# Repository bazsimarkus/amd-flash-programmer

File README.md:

# amd-flash-programmer
A simple Arduino-based flash memory programmer for AM29F010 and AM29F040B series flash chips.

---

## Table of Contents

- [Overview](#overview)
- [Features](#features)
- [Hardware](#hardware)
  - [Schematic](#schematic)
  - [How It Works](#how-it-works)
  - [Bill of Materials](#bill-of-materials)
  - [Pin Mapping](#pin-mapping)
  - [Supported Chips](#supported-chips)
  - [PCB](#pcb)
- [Firmware](#firmware)
  - [Architecture](#architecture)
  - [Serial Protocol](#serial-protocol)
  - [Uploading the Firmware](#uploading-the-firmware)
- [Client Software](#client-software)
  - [Installation](#installation)
  - [Usage](#usage)
- [How to Use](#how-to-use)
  - [Connect](#connect)
  - [Read Chip ID](#read-chip-id)
  - [Read Memory](#read-memory)
  - [Erase Chip](#erase-chip)
  - [Write File](#write-file)
  - [Verify](#verify)
- [Performance](#performance)
- [Known Limitations & Future Ideas](#known-limitations--future-ideas)
- [Personal Notes](#personal-notes)
- [Inspirations & Credits](#inspirations--credits)

---

## Overview

I always needed a way to program AM29F040B flash chips without spending money on an expensive universal programmer. My [ATmega32-based MOD tracker player](https://github.com/bazsimarkus/avr-mod-player) uses this chip to store `.mod` tracker files, and to be able to write new music onto the player I decided to design a dedicated programmer board. These chips were also used in Game Boy Color cartridges, among other things, so there is a retro community out there that might find this useful too.

My main inspiration was [TommyPROM](https://github.com/TomNisbet/TommyPROM), but TommyPROM is a general-purpose EEPROM programmer and doesn't directly support the AMD 29F-series flash command sequences. The AM29F010 and AM29F040B use software-controlled erase and programming cycles with specific unlock addresses - you can't just write to them like a parallel EEPROM. So I designed my own board, wrote the Arduino firmware from scratch, and also created a Python GUI client to make the whole process beginner-friendly.

The result is a simple, easy-to-build board that does exactly what I need: read, write, erase, and verify AM29F-series flash chips over USB.

---

## Features

- **Read** - full chip or custom hex address range, displayed in a live hex viewer
- **Write** - binary files to flash with byte-by-byte handshake protocol
- **Erase** - full chip erase with proper DQ7 data polling
- **Verify** - automatic post-write verification or manual verify against any file
- **Chip ID** - reads manufacturer and device ID via autoselect mode
- **Hex Viewer** - colour-coded hex dump with ASCII column in the GUI
- **Event Log** - timestamped log of all operations, exportable to file
- **COM port auto-detection** - scans and lists available serial ports
- Supports **AM29F010** (128 KB) and **AM29F040B** (512 KB)
- Beginner-friendly - easy to solder, easy to flash, easy to use
- All through-hole components - no SMD soldering required
- Powered directly from USB via the Arduino Nano

---

## Hardware

### Schematic

The full KiCad project including schematic, PCB layout, and netlist is available in the `schematic/` folder.

---

### How It Works

The circuit is straightforward. There are only a few building blocks, and each has a clear job.

**Arduino Nano (A1)** - This is the brain of the board. It handles USB serial communication with the PC at 115200 baud, generates the timing for the shift registers, drives the flash chip's control signals (CE#, OE#, WE#), and reads/writes the 8-bit data bus. It is powered directly from the USB cable, and provides 5V to the rest of the circuit from its onboard regulator.

**74HC595 Shift Registers (U2, U3)** - The AM29F040B has 19 address lines (A0-A18), which is far more than what the Arduino Nano has available as spare GPIO. The solution is to use two 74HC595 shift registers daisy-chained together. These are 8-bit serial-in, parallel-out shift registers. The Arduino sends 16 bits of address data serially using just three control lines (serial data on A5, shift clock on A3, and latch clock on A4), and the two shift registers present all 16 bits simultaneously on their parallel outputs. U2 provides address lines A0-A7 (low byte), and its serial overflow output (QH') feeds into U3 which provides A8-A15 (high byte). The remaining three address lines (A16, A17, A18) are driven directly from the Nano's analog pins A0, A1, and A2 - there is no need to shift those since there are only three of them and the Nano has enough free pins.

**Flash Chip Socket (U1)** - A 32-pin ZIF (Zero Insertion Force) Textool socket. ZIF sockets have a lever that opens and closes the contacts, so you can insert and remove DIP chips without bending any pins. This is important because if you are regularly swapping flash chips in and out, a standard friction-fit DIP socket will eventually damage the pins or wear out. The ZIF socket is the most expensive component on the board, but it is worth it.

**Data Bus (D2-D9)** - The flash chip's 8-bit data bus (DQ0-DQ7) connects directly to Arduino Nano pins D2 through D9. These pins are mapped to PORTD bits 2-7 and PORTB bits 0-1 in the firmware. During a read, the Arduino sets these as inputs and reads the parallel data from the flash. During a write, it sets them as outputs and drives the data to be programmed.

**Control Signals (D10, D11, D12)** - Three active-low control signals go from the Arduino to the flash chip:
- **CE#** (Chip Enable) on D10 - must be low for the chip to respond to any bus cycle
- **OE#** (Output Enable) on D11 - drives the chip's data outputs onto the bus during a read
- **WE#** (Write Enable) on D12 - latches data into the chip during a write or command cycle

All three have 10kΩ pull-up resistors (R1, R2, R3) to +5V. This is a safety measure: during Arduino power-up, reset, or bootloader execution, the GPIO pins are momentarily tri-stated (floating). Without the pull-ups, the flash chip might interpret random noise on CE#, OE#, and WE# as valid bus cycles and get confused or, in a worst case, accidentally erase data. The pull-ups ensure all control signals default to their inactive (high) state until the firmware explicitly takes control.

**LEDs (D1, D2)** - A red LED for power indication (always on when USB is connected) and a yellow LED for status (blinks during operations). Each LED has a 470Ω series resistor (R4 for the power LED, R5 for the status LED) to limit the current to a safe value. The status LED is connected to D13, which is the Arduino's built-in LED pin.

**Decoupling Capacitors (C1, C2, C3, C4)** - Three 100nF ceramic capacitors are placed near the power supply pins of U1 (flash chip), U2, and U3 (shift registers). These are standard bypass capacitors that filter out high-frequency noise on the power supply lines. Without them, the rapid switching of the digital logic creates voltage spikes that can cause unreliable operation, especially on the flash chip which has tight timing requirements. C4 is a 47µF electrolytic capacitor providing bulk energy storage for the entire board, smoothing out any supply droop when the flash chip draws current during erase or programming operations.

---

### Bill of Materials

| Reference | Qty | Value / Part | Description |
|-----------|-----|--------------|-------------|
| A1 | 1 | Arduino Nano v3.x | Main microcontroller module (ATmega328P) |
| U1 | 1 | 32-pin ZIF Socket (Textool) | Zero-insertion-force socket for flash chip |
| U2 | 1 | 74HC595 (DIP-16) | 8-bit shift register - address lines A0-A7 |
| U3 | 1 | 74HC595 (DIP-16) | 8-bit shift register - address lines A8-A15 |
| D1 | 1 | LED 5mm RED | Power indicator |
| D2 | 1 | LED 5mm YELLOW | Status indicator (directly controlled via D13) |
| R1, R2 | 2 | 10kΩ | Pull-up resistors for CE# and OE# |
| R3 | 1 | 10kΩ | Pull-up resistor for WE# |
| R4 | 1 | 470Ω | Current limiting resistor for power LED |
| R5 | 1 | 470Ω | Current limiting resistor for status LED |
| C1, C2, C3 | 3 | 100nF ceramic | Decoupling capacitors (one per IC) |
| C4 | 1 | 47µF electrolytic | Bulk power filtering |

All components are through-hole and readily available from any electronics supplier. The total component cost (excluding the Arduino Nano and ZIF socket) is under 2 EUR.

---

### Pin Mapping

The Arduino Nano's pins are allocated as follows:

| Arduino Pin | Port | Function |
|-------------|------|----------|
| D2-D9 | PORTD[2:7], PORTB[0:1] | Flash data bus DQ0-DQ7 |
| D10 | PORTB2 | Flash CE# (active low) |
| D11 | PORTB3 | Flash OE# (active low) |
| D12 | PORTB4 | Flash WE# (active low) |
| D13 | PORTB5 | Status LED |
| A0 | PORTC0 | Flash A18 (directly driven) |
| A1 | PORTC1 | Flash A17 (directly driven) |
| A2 | PORTC2 | Flash A16 (directly driven) |
| A3 | PORTC3 | Shift register SRCLK (clock) |
| A4 | PORTC4 | Shift register RCLK (latch) |
| A5 | PORTC5 | Shift register SER (serial data) |

The two 74HC595 shift registers are daisy-chained: U2 provides A0-A7 and its serial overflow (QH') feeds into U3 which provides A8-A15. This gives 16 address bits via SPI-like shifting, plus 3 bits driven directly, totalling 19 address lines - enough for 512 KB.

---

### Supported Chips

| Chip | Size | Unlock 1 | Unlock 2 | Mfr ID | Dev ID |
|------|------|----------|----------|--------|--------|
| AM29F010 | 128 KB (131,072 bytes) | 0x5555 | 0x2AAA | 0x01 | 0x20 |
| AM29F040B | 512 KB (524,288 bytes) | 0x0555 | 0x02AA | 0x01 | 0xA4 |

Note that the two chips use different unlock address sequences - the firmware handles this automatically based on the selected chip type.

---

### PCB

The PCB is revision **v1.0**, designed in KiCad 9.0.6. It is a single-sided through-hole board manufactured with black soldermask and white silkscreen. The board was manufactured by JLCPCB. All components are through-hole for ease of hand assembly - this is a beginner-friendly build that anyone with basic soldering skills can complete in under an hour.

The full KiCad project including schematic, PCB layout, and Gerber files is in the `schematic/` folder.

---

## Firmware

### Architecture

The firmware (`amd-flash-programmer.ino`) is written in C/C++ using the Arduino framework, but with direct port manipulation for speed. It runs at 115200 baud and implements a simple text-based command protocol over serial.

Key design decisions:

- **Direct port manipulation** - the data bus and control signals are manipulated via `PORTB`, `PORTD`, and `PORTC` registers rather than `digitalWrite()`, which would be too slow for the programming timing requirements.
- **Byte-by-byte handshake for writes** - the Arduino Nano has only a 64-byte UART receive buffer. At 115200 baud, bytes arrive at ~11 KB/s, but programming a byte to flash takes up to 200µs. A naive burst approach would overflow the buffer. Instead, the firmware programs one byte, sends a single `'K'` ACK character, and the host waits for that ACK before sending the next byte. This is slower (~0.5 KB/s) but 100% reliable.
- **DQ7 data polling** - both byte programming and chip erase use the AMD-standard DQ7 polling algorithm to detect completion, with DQ5 error checking as a fallback.
- **70-second erase timeout** - the AM29F040B datasheet specifies a maximum chip erase time of ~64 seconds, so the firmware allows up to 70 seconds before declaring a timeout.

---

### Serial Protocol

All commands are ASCII, terminated with `\n`. The Arduino responds with ASCII status lines.

| Command | Description | Response |
|---------|-------------|----------|
| `?` | Status query | `STATUS:<chip_name> SIZE:<bytes>` |
| `C<idx>` | Select chip (0=AM29F010, 1=AM29F040B) | `CHIP_OK:<name>` or `CHIP_ERR:...` |
| `I` | Read chip ID (autoselect mode) | `MFR:<hex> DEV:<hex>` |
| `R <start_hex> <end_hex>` | Read address range | `RSTART <count>` + raw bytes + `REND` |
| `E` | Full chip erase | `ERASE_START` → `ERASE_OK` or `ERASE_FAIL` |
| `W <size_dec>` | Write `<size>` bytes | `WREADY` → (byte-by-byte with `K` ACKs) → `WDONE:<n>` |

---

### Uploading the Firmware

1. Open `amd-flash-programmer.ino` in the Arduino IDE
2. Select **Board:** `Arduino Nano`
3. Select **Processor:** `ATmega328P` (or `ATmega328P (Old Bootloader)` depending on your board)
4. Select the correct COM port
5. Click **Upload**

No external libraries are required - the firmware uses only standard AVR headers and the Arduino Serial library.

---

## Client Software

The Python GUI client (`amd-flash-programmer-client.py`) provides a complete graphical interface for interacting with the programmer board.

### Installation

Requires Python 3.x with `pyserial`:

```bash
pip install pyserial
python amd-flash-programmer-client.py
```

The client is built entirely with `tkinter` (included with Python) and `pyserial` - no other dependencies.

---

### Usage

The GUI is split into several sections:

- **Connection panel** - COM port selection, baud rate, connect/disconnect
- **Chip panel** - chip type selection (AM29F010 / AM29F040B), Apply, Read Chip ID
- **Operations panel** - Read Memory, Erase Chip, Write File, Verify vs File, Save Binary
- **Progress bar** - shows real-time progress with speed and ETA
- **Read range** - configurable start/end addresses (hex), Full Chip button
- **Event Log** (left panel) - timestamped log of all events, saveable to file
- **Hex View** (right panel) - colour-coded hex dump with address, hex bytes, and ASCII columns

The client includes a built-in chip database with known manufacturer IDs (AMD/Spansion, Fujitsu, Atmel, ST Micro, SST, Macronix, Winbond, etc.) and will display human-readable names when a chip ID is read.

---

## How to Use

### Connect

1. Insert the flash chip into the ZIF socket - **pin 1 goes to the top** (lever side)
2. Close the ZIF lever to lock the chip in place
3. Connect the Arduino Nano to your computer via USB
4. Launch the Python client
5. Select the correct COM port from the dropdown and click **Connect**
6. The client will reset the Arduino and wait for it to boot (~3 seconds)

### Read Chip ID

Click **Read Chip ID** to enter autoselect mode and read back the manufacturer and device ID bytes. This confirms the chip is correctly inserted and the wiring is working. If you get `FF/FF`, check your connections.

### Read Memory

- Set the start and end addresses in hex, or click **Full Chip** to auto-fill
- Click **Read Memory**
- The contents will be displayed in the Hex View panel
- Click **Save Binary** to export to a `.bin` or `.rom` file

### Erase Chip

Click **Erase Chip** to perform a full chip erase. The operation uses the standard AMD 6-bus-cycle erase sequence and polls DQ7 for completion. Typical erase time is 1-5 seconds, maximum ~64 seconds per datasheet.

> ⚠️ **Important:** Flash chips must be fully erased before writing. You cannot overwrite individual bytes without erasing the entire chip (or at least the sector) first.

### Write File

- Click **Write File...** and select a binary file (`.bin`, `.rom`, `.img`)
- The file will be written byte-by-byte starting at address 0x000000
- Progress is shown in real-time with speed and ETA
- If **Verify after write** is checked, a full readback comparison runs automatically after writing

### Verify

Click **Verify vs File...** to read the chip and compare it byte-for-byte against a reference file. The client will report pass or fail, listing the first 10 mismatches if verification fails.

---

## Performance

| Operation | Speed | Time (full AM29F040B, 512 KB) |
|-----------|-------|-------------------------------|
| Read | ~11.5 KB/s | ~44.6 seconds |
| Write (byte-by-byte handshake) | ~0.5 KB/s | ~17 minutes |
| Erase | - | 1-5 seconds typical |

The write speed is intentionally slow to ensure reliability. The byte-by-byte ACK handshake prevents UART buffer overflow, which was a problem with burst-mode approaches. For typical use cases (small ROMs, tracker files, cartridge images) the speed is perfectly acceptable.

---

## Known Limitations & Future Ideas

**Write speed** - at ~0.5 KB/s, writing a full 512 KB chip takes about 17 minutes. This is the price of the reliable byte-by-byte handshake protocol. A future improvement could use small block transfers (e.g., 32 bytes at a time) with flow control, but for my use case the current speed is fine.

**No sector erase** - the firmware currently only supports full chip erase. The AM29F040B supports sector-by-sector erase (64 KB sectors), which would be useful for partial updates. This would be straightforward to add but I haven't needed it yet.

**No write offset** - writes always start at address 0x000000. Supporting an arbitrary start address for writes would be a nice addition for partial ROM updates.

**Single-chip wiring** - the board is wired specifically for 32-pin DIP flash chips in the AM29F family. Other pin-compatible chips (like SST39SF040 or similar 5V parallel flash) may work with minor firmware modifications to the unlock sequences, but I haven't tested them.

**No 3.3V support** - the board runs at 5V from the Arduino Nano's USB supply. Some newer flash chips require 3.3V - those are not supported without a level shifter modification.

---

## Personal Notes

This project came about because I needed to program flash chips for my MOD tracker player. I could have bought a TL866 or similar universal programmer, but where is the fun in that? I wanted something I could understand completely, something I could fix if it broke, and something I could share with other hobbyists who might be in the same situation.

The board is deliberately simple - no SMD components, no complex power supply, no FPGA. Just an Arduino Nano, two shift registers, a ZIF socket, and some passives. If you can solder a through-hole kit, you can build this. The Python client is similarly straightforward - one file, one dependency (`pyserial`), and it runs on Windows, Linux, and macOS.

I spent more time debugging the write protocol than anything else. The original approach was to stream bytes at full serial speed and let the Arduino buffer them, but the 64-byte UART buffer combined with variable programming times (0xFF bytes are instant, non-FF bytes take up to 200µs) meant that overflow was inevitable for non-trivial files. The byte-by-byte handshake is slower but it has never failed on me.

The DQ7 polling implementation also took some careful reading of the datasheet. The AMD flash programming algorithm is well-documented but subtle - you need to check DQ5 (timeout flag) as well as DQ7 (data polling), and you need to do a final read after DQ5 triggers to avoid false failures. Getting this right meant the difference between a programmer that works on the bench and one that works reliably every time.

---

## Inspirations & Credits

- **Tom Nisbet** - [TommyPROM](https://github.com/TomNisbet/TommyPROM)
  The project that showed me an Arduino-based EEPROM/flash programmer was viable and well within reach.

- **AMD / Spansion** - AM29F040B Datasheet
  The reference for all programming sequences, timing, and polling algorithms.

- **KiCad** - [kicad.org](https://www.kicad.org/)
  Schematic and PCB design.

- **Python** / **pyserial** / **tkinter**
  The client software stack.

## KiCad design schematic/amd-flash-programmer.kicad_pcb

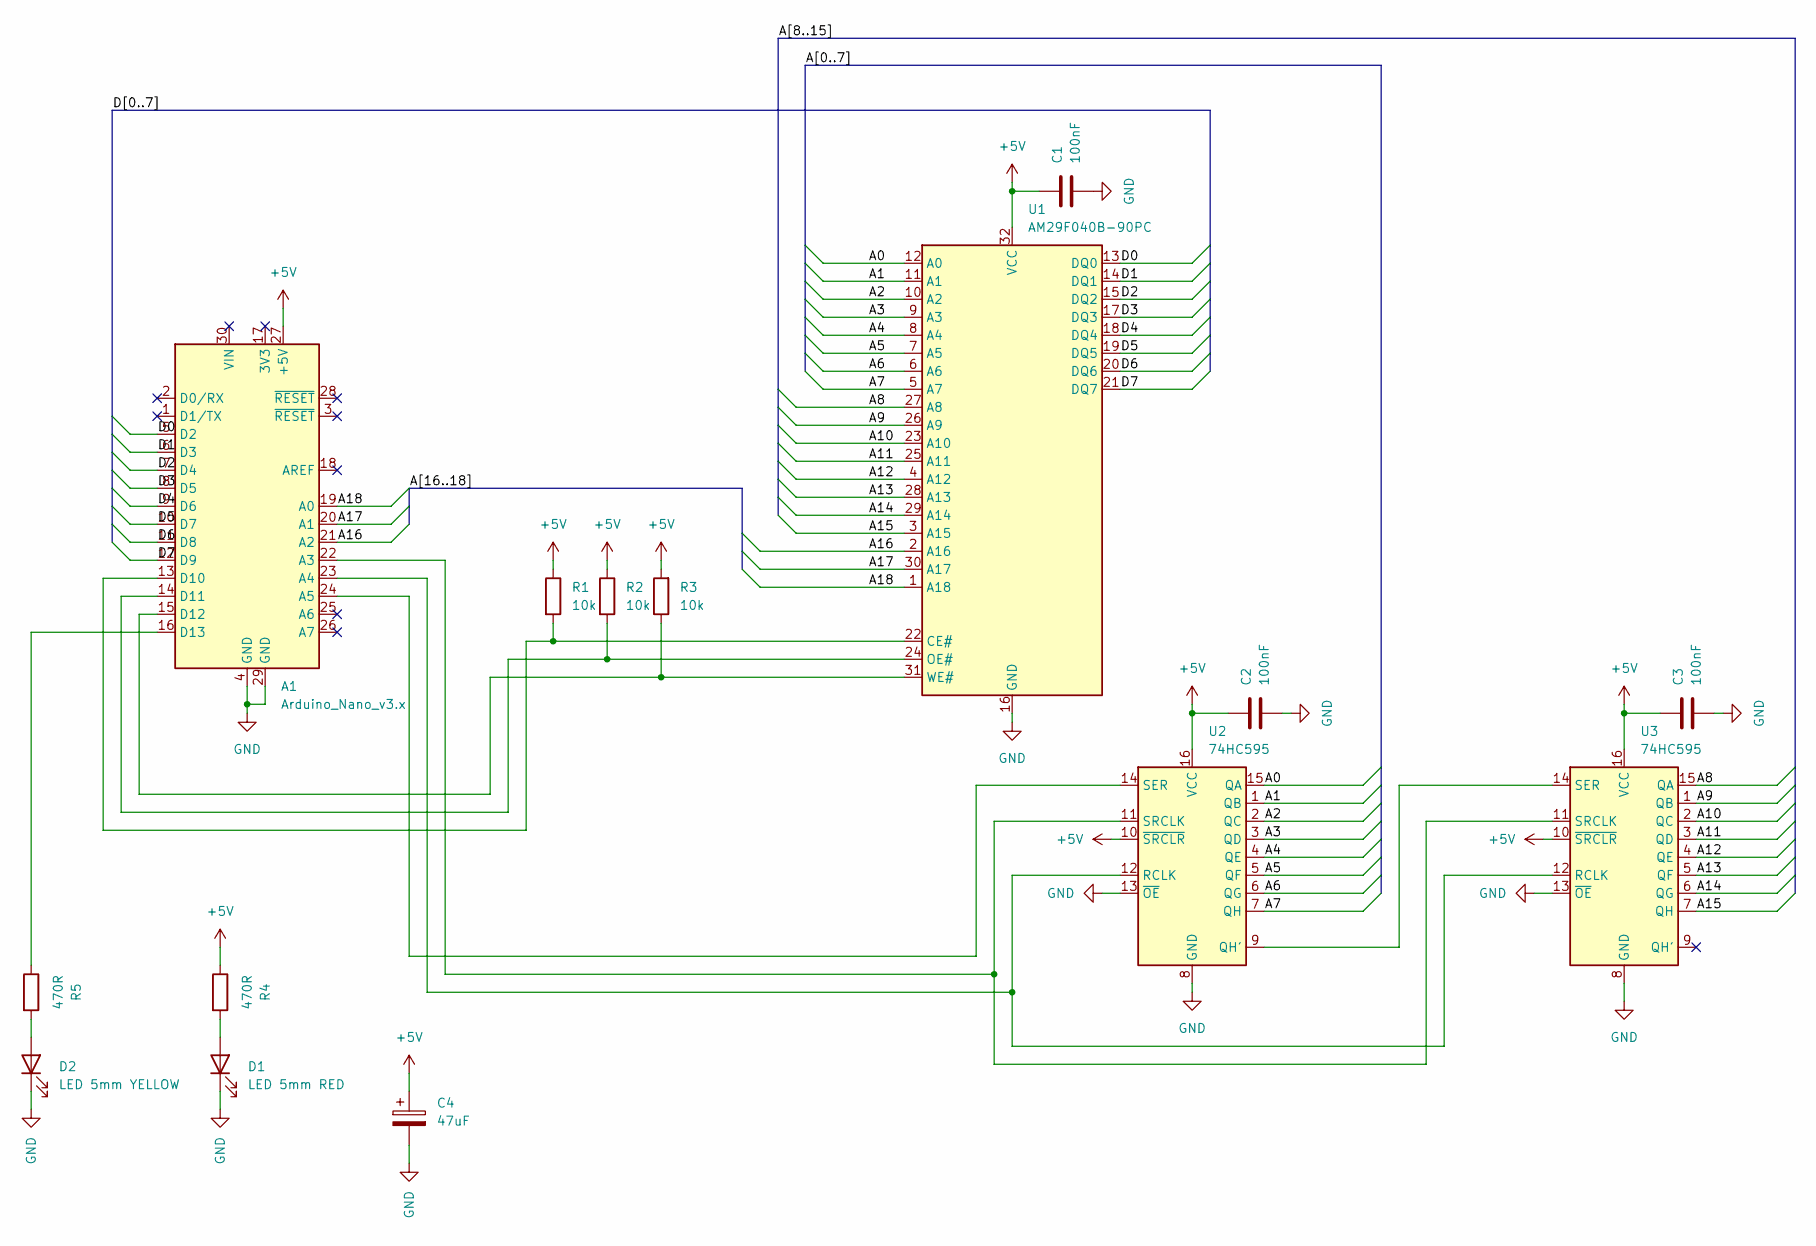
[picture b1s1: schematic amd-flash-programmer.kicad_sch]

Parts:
A1: Arduino_Nano_v3.x; Arduino_Nano
C1, C2, C3: 100nF; C_100nF_L7.0mm_W2.5mm_P5.00mm
C4: 47uF; CP_Radial_D5.0mm_P2.00mm
D1: LED 5mm RED; LED_D5.0mm_RED
D2: LED 5mm YELLOW; LED_D5.0mm_YELLOW
R1, R2, R3: 10k; R_10k_Axial_DIN0207
R4, R5: 470R; R_470_Axial_DIN0207
U1: AM29F040B-90PC; DIP_Socket-32_W11.9mm_W12.7mm_W15.24mm_W17.78mm_W18.5mm_3M_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
U2, U3: 74HC595; DIP-16_W7.62mm

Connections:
+5V: A1.27 (+5V), C1.1, C2.1, C3.1, C4.1, R1.1, R2.1, R3.2, R4.1, U1.32 (VCC), U2.10 (~SRCLR), U2.16 (VCC), U3.10 (~SRCLR), U3.16 (VCC)
/A0: U1.12 (A0), U2.15 (QA)
/A1: U1.11 (A1), U2.1 (QB)
/A2: U1.10 (A2), U2.2 (QC)
/A3: U1.9 (A3), U2.3 (QD)
/A4: U1.8 (A4), U2.4 (QE)
/A5: U1.7 (A5), U2.5 (QF)
/A6: U1.6 (A6), U2.6 (QG)
/A7: U1.5 (A7), U2.7 (QH)
/A8: U1.27 (A8), U3.15 (QA)
/A9: U1.26 (A9), U3.1 (QB)
/A10: U1.23 (A10), U3.2 (QC)
/A11: U1.25 (A11), U3.3 (QD)
/A12: U1.4 (A12), U3.4 (QE)
/A13: U1.28 (A13), U3.5 (QF)
/A14: U1.29 (A14), U3.6 (QG)
/A15: U1.3 (A15), U3.7 (QH)
/A16: A1.21 (A2), U1.2 (A16)
/A17: A1.20 (A1), U1.30 (A17)
/A18: A1.19 (A0), U1.1 (A18)
/D0: A1.5 (D2), U1.13 (DQ0)
/D1: A1.6 (D3), U1.14 (DQ1)
/D2: A1.7 (D4), U1.15 (DQ2)
/D3: A1.8 (D5), U1.17 (DQ3)
/D4: A1.9 (D6), U1.18 (DQ4)
/D5: A1.10 (D7), U1.19 (DQ5)
/D6: A1.11 (D8), U1.20 (DQ6)
/D7: A1.12 (D9), U1.21 (DQ7)
GND: A1.4 (GND), A1.29 (GND), C1.2, C2.2, C3.2, C4.2, D1.1 (K), D2.1 (K), U1.16 (GND), U2.8 (GND), U2.13 (~OE), U3.8 (GND), U3.13 (~OE)
unnamed: A1.22 (A3), U2.11 (SRCLK), U3.11 (SRCLK)
unnamed: A1.23 (A4), U2.12 (RCLK), U3.12 (RCLK)
unnamed: A1.24 (A5), U2.14 (SER)
unnamed: A1.13 (D10), R1.2, U1.22 (CE#)
unnamed: A1.14 (D11), R2.2, U1.24 (OE#)
unnamed: A1.15 (D12), R3.1, U1.31 (WE#)
unnamed: A1.16 (D13), R5.1
unnamed: D1.2 (A), R4.2
unnamed: D2.2 (A), R5.2
unnamed: U2.9 (QH'), U3.14 (SER)

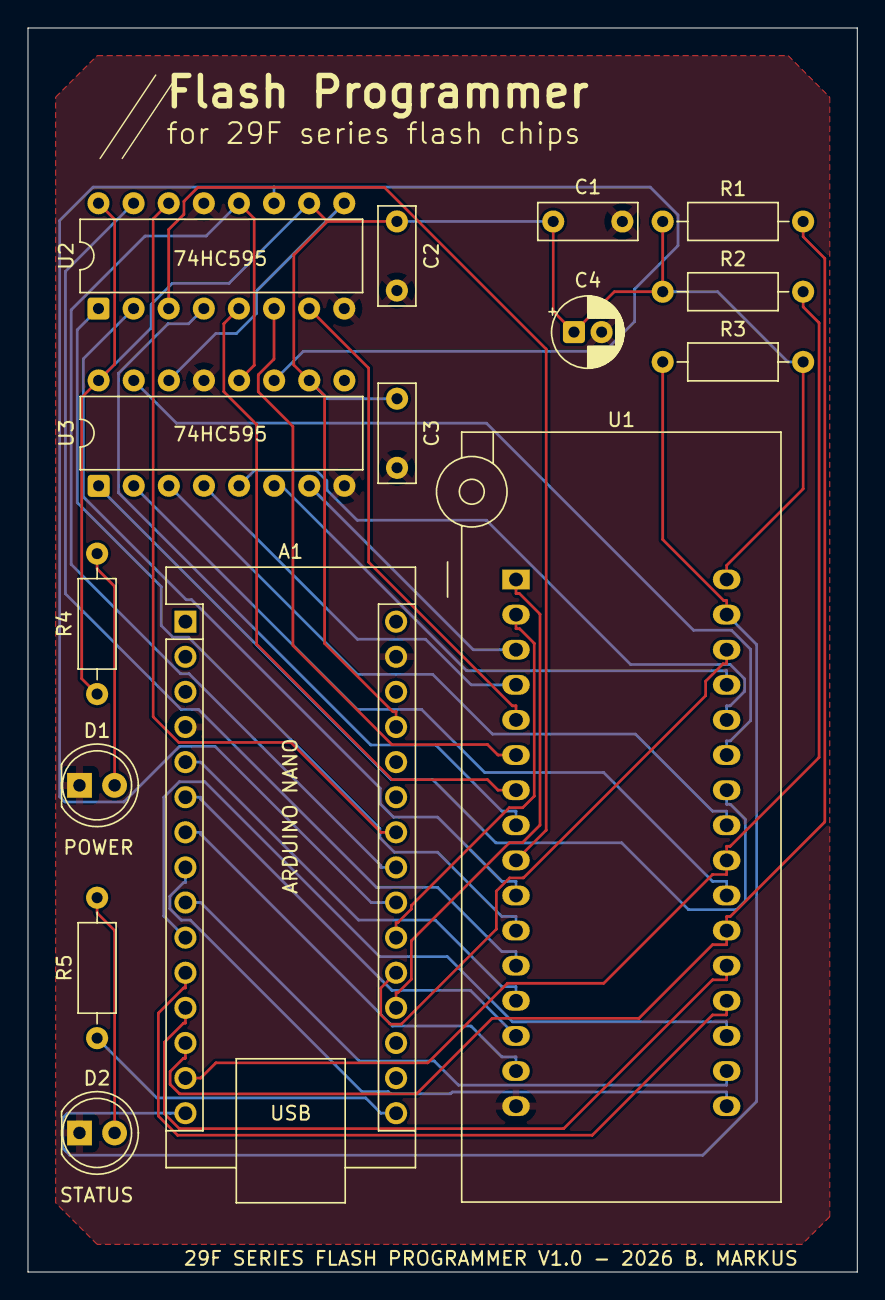
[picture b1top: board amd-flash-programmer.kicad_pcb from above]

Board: 2 copper layers, 60.0 x 90.0 mm, 15 parts (0 on the bottom side), 39 nets.

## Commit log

2026-02-20 Base code files added
2026-02-21 GUI updated, dropdown bugs fixed, help button added
2026-02-22 Folders renamed
2026-02-22 Schematic files added
2026-03-03 PCB design added to schematic folder
2026-03-05 PCB rerouted without vias, silkscreen updated
2026-03-23 PCB updated
2026-05-07 Images added
